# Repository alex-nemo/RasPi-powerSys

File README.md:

# RasPi-powerSys
UPS for Raspberry Pi with power status monitoring

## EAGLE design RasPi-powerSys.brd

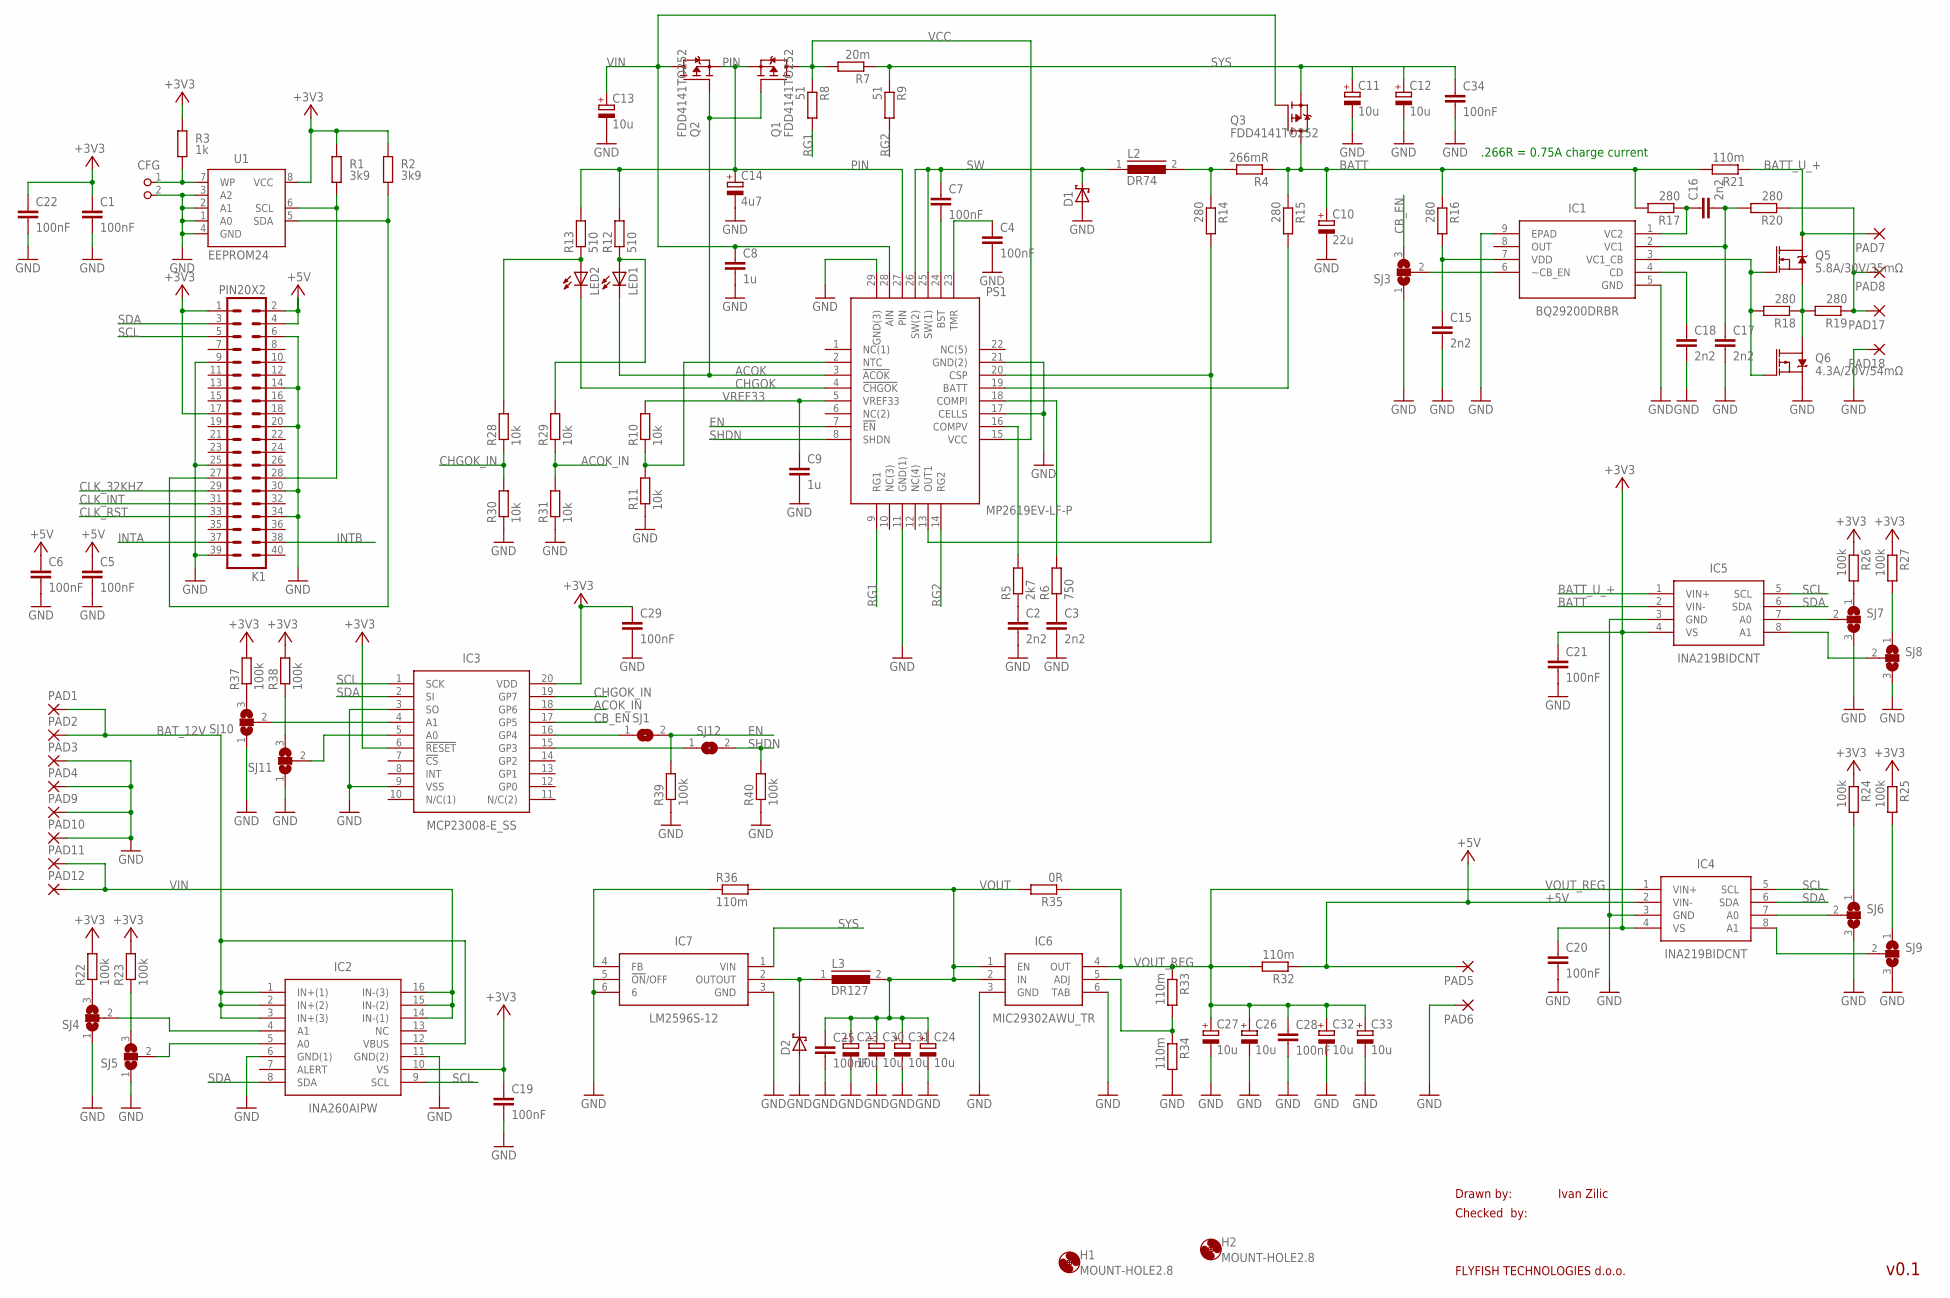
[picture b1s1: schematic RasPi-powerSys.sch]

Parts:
C1, C4, C5, C6, C7, C19, C20, C21, C22, C25, C28, C29, C34: 100nF; C0805K
C2, C3, C15, C16, C17, C18: 2n2; C0805K
C8, C9: 1u; C0805K
C10: 22u; SMC_D
C11, C23, C24, C26, C27, C30, C31, C32, C33: 10u; SMC_E
C12, C13: 10u; SMC_D
C14: 4u7; SMC_D
CFG: PIN2_100; PIN_W_2
D1, D2: SCHOTTKY-DIODESMD; SMB
H1, H2: MOUNT-HOLE2.8; 2,8
IC1: BQ29200DRBR; SON65P300X300X100-9N
IC2: INA260AIPW; SOP65P640X120-16N
IC3: MCP23008-E_SS; SOP65P780X200-20N
IC4, IC5: INA219BIDCNT; SOT65P280X145-8N
IC6: MIC29302AWU_TR; 5-PIN-TO-263(U)
IC7: LM2596S-12; 5-PIN-TO-263(U)
K1: PIN20X2; PIN_20X2
L2: DR74
L3: DR127
LED1, LED2: LEDCHIPLED_0805; CHIPLED_0805
PAD1, PAD2, PAD3, PAD4, PAD5, PAD6, PAD7, PAD8, PAD9, PAD10, PAD11, PAD12, PAD17, PAD18: 3,81/1,4
PS1: MP2619EV-LF-P; QFN50P400X500X100-29N
Q1, Q2, Q3: FDD4141TO252; TO252
Q5: 5.8A/30V/35mΩ; SOT23-3
Q6: 4.3A/20V/54mΩ; SOT23-3
R1, R2: 3k9; M0805; TOLERANCE 5%
R3: 1k; M0805; TOLERANCE 5%
R4: 266mR; R1206
R5: 2k7; R0805
R6: 750; R0805
R7: 20m; R0805
R8, R9: 51; R0805
R10, R11, R28, R29, R30, R31: 10k; R0805
R12, R13: 510; R0805
R14, R15, R16: 280; R0805
R17, R18, R19, R20: 280; R1206
R21, R33, R34, R36: 110m; R0805
R22, R23, R24, R25, R26, R27, R37, R38, R39, R40: 100k; R0805
R32: 110m; R1206
R35: 0R; R1206
SJ1, SJ12: SJ
SJ3, SJ4, SJ5, SJ6, SJ7, SJ8, SJ9, SJ10, SJ11: SJ2W; SJ_2
U1: EEPROM24; SOIC8

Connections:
+3V3: C1.1, C19.1, C20.1, C21.1, C22.1, C29.1, IC2.10 (VS), IC3.6 (!RESET), IC3.20 (VDD), IC4.4 (VS), IC5.4 (VS), K1.1, K1.17, R1.2, R2.2, R3.2, R22.2, R23.2, R24.1, R25.1, R26.1, R27.1, R37.2, R38.2, U1.8 (VCC)
+5V: C5.1, C6.1, IC4.2 (VIN-), K1.2, K1.4, PAD5.1, R32.1
ACOK: LED1.C, PS1.3 (!ACOK), Q1.1 (G), Q2.1 (G)
ACOK_IN: IC3.18 (GP6), R29.1, R31.2
ADJ: IC6.5 (ADJ), R33.2, R34.1
BATT: C10.+, IC5.2 (VIN-), Q3.3 (D), R4.1, R15.1, R16.1, R17.2, R21.2
BATT_U_+: IC5.1 (VIN+), PAD7.1, Q5.3 (D), R21.1
BAT_12V: IC2.1 (IN+(1)), IC2.2 (IN+(2)), IC2.3 (IN+(3)), IC2.12 (VBUS), PAD1.1, PAD2.1
CB_EN: IC3.17 (GP5), SJ3.3
CHGOK: LED2.C, PS1.4 (!CHGOK)
CHGOK_IN: IC3.19 (GP7), R28.1, R30.2
CLK_32KHZ: K1.29
CLK_INT: K1.31
CLK_RST: K1.33
EN: PS1.7 (!EN), R39.2, SJ1.2
GND: C1.2, C2.2, C3.2, C4.2, C5.2, C6.2, C8.2, C9.2, C10.-, C11.-, C12.-, C13.-, C14.-, C15.2, C17.2, C18.2, C19.2, C20.2, C21.2, C22.2, C23.-, C24.-, C25.2, C26.-, C27.-, C28.2, C29.2, C30.-, C31.-, C32.-, C33.-, C34.2, CFG.2, D1.A, D2.A, IC1.5 (GND), IC1.9 (EPAD), IC2.6 (GND(1)), IC2.11 (GND(2)), IC3.3 (SO), IC3.9 (VSS), IC4.3 (GND), IC5.3 (GND), IC6.3 (GND), IC6.6 (TAB), IC7.3 (GND), IC7.5 (!ON!/OFF), IC7.6, K1.6, K1.9, K1.14, K1.20, K1.25, K1.30, K1.34, K1.39, PAD3.1, PAD4.1, PAD6.1, PAD9.1, PAD10.1, PAD18.1, PS1.11 (GND(1)), PS1.17 (CELLS), PS1.21 (GND(2)), PS1.29 (GND(3)), Q6.2 (S), R11.1, R30.1, R31.1, R34.2, R39.1, R40.1, SJ3.1, SJ4.1, SJ5.1, SJ6.3, SJ7.3, SJ8.3, SJ9.3, SJ10.1, SJ11.1, U1.1 (A0), U1.2 (A1), U1.3 (A2), U1.4 (GND)
INTA: K1.37
INTB: K1.38
unnamed: PS1.16 (COMPV), R5.2
unnamed: PS1.18 (COMPI), R6.2
unnamed: CFG.1, R3.1, U1.7 (WP)
unnamed: C2.1, R5.1
unnamed: C3.1, R6.1
unnamed: C4.1, PS1.23 (TMR)
unnamed: IC3.16 (GP4), SJ1.1
unnamed: C15.1, IC1.7 (VDD), R16.2
unnamed: C7.2, PS1.24 (BST)
unnamed: L2.2, R4.2, R14.1
unnamed: IC1.6 (~CB_EN), SJ3.2
unnamed: PS1.2 (NTC), R10.1, R11.2
unnamed: Q5.2 (S), Q6.3 (D), R18.1, R19.2
unnamed: IC3.15 (GP3), SJ12.1
unnamed: PS1.19 (BATT), R15.2
unnamed: LED1.A, R12.1, R29.2
unnamed: K1.28, R1.1, U1.6 (SCL)
unnamed: LED2.A, R13.1, R28.2
unnamed: C18.1, IC1.4 (CD)
unnamed: PS1.13 (OUT1), PS1.20 (CSP), R14.2
unnamed: PAD8.1, PAD17.1, R19.1, R20.1
unnamed: C16.2, C17.1, IC1.2 (VC1), R20.2
unnamed: K1.27, R2.1, U1.5 (SDA)
unnamed: C16.1, IC1.1 (VC2), R17.1
unnamed: IC1.3 (VC1_CB), Q5.1 (G), Q6.1 (G), R18.2
unnamed: IC2.5 (A0), SJ5.2
unnamed: IC2.4 (A1), SJ4.2
unnamed: R22.1, SJ4.3
unnamed: R23.1, SJ5.3
unnamed: R26.2, SJ7.1
unnamed: R27.2, SJ8.1
unnamed: IC4.8 (A1), SJ9.2
unnamed: IC4.7 (A0), SJ6.2
unnamed: IC5.8 (A1), SJ8.2
unnamed: IC5.7 (A0), SJ7.2
unnamed: R37.1, SJ10.3
unnamed: D2.C, IC7.2 (OUTOUT), L3.1
unnamed: R24.2, SJ6.1
unnamed: R25.2, SJ9.1
unnamed: IC7.4 (FB), R36.1
unnamed: IC3.4 (A1), SJ10.2
unnamed: IC3.5 (A0), SJ11.2
unnamed: R38.1, SJ11.3
PIN: C14.+, PS1.27 (PIN), Q1.2 (S), Q2.2 (S), R12.2, R13.2
RG1: PS1.9 (RG1), R8.2
RG2: PS1.14 (RG2), R9.2
SCL: IC2.9 (SCL), IC3.1 (SCK), IC4.5 (SCL), IC5.5 (SCL), K1.5
SDA: IC2.8 (SDA), IC3.2 (SI), IC4.6 (SDA), IC5.6 (SDA), K1.3
SHDN: PS1.8 (SHDN), R40.2, SJ12.2
SW: C7.1, D1.C, L2.1, PS1.25 (SW(1)), PS1.26 (SW(2))
SYS: C11.+, C12.+, C34.1, IC7.1 (VIN), Q3.2 (S), R7.1, R9.1
VCC: PS1.15 (VCC), Q1.3 (D), R7.2, R8.1
VIN: C8.1, C13.+, IC2.14 (IN-(1)), IC2.15 (IN-(2)), IC2.16 (IN-(3)), PAD11.1, PAD12.1, PS1.28 (AIN), Q2.3 (D), Q3.1 (G)
VOUT: C23.+, C24.+, C25.1, C30.+, C31.+, IC6.1 (EN), IC6.2 (IN), L3.2, R35.2, R36.2
VOUT_REG: C26.+, C27.+, C28.1, C32.+, C33.+, IC4.1 (VIN+), IC6.4 (OUT), R32.2, R33.1, R35.1
VREF33: C9.1, PS1.5 (VREF33), R10.2

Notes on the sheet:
Drawn by:
Checked by:
FLYFISH TECHNOLOGIES d.o.o.
Ivan Zilic
v0.1
.266R = 0.75A charge current

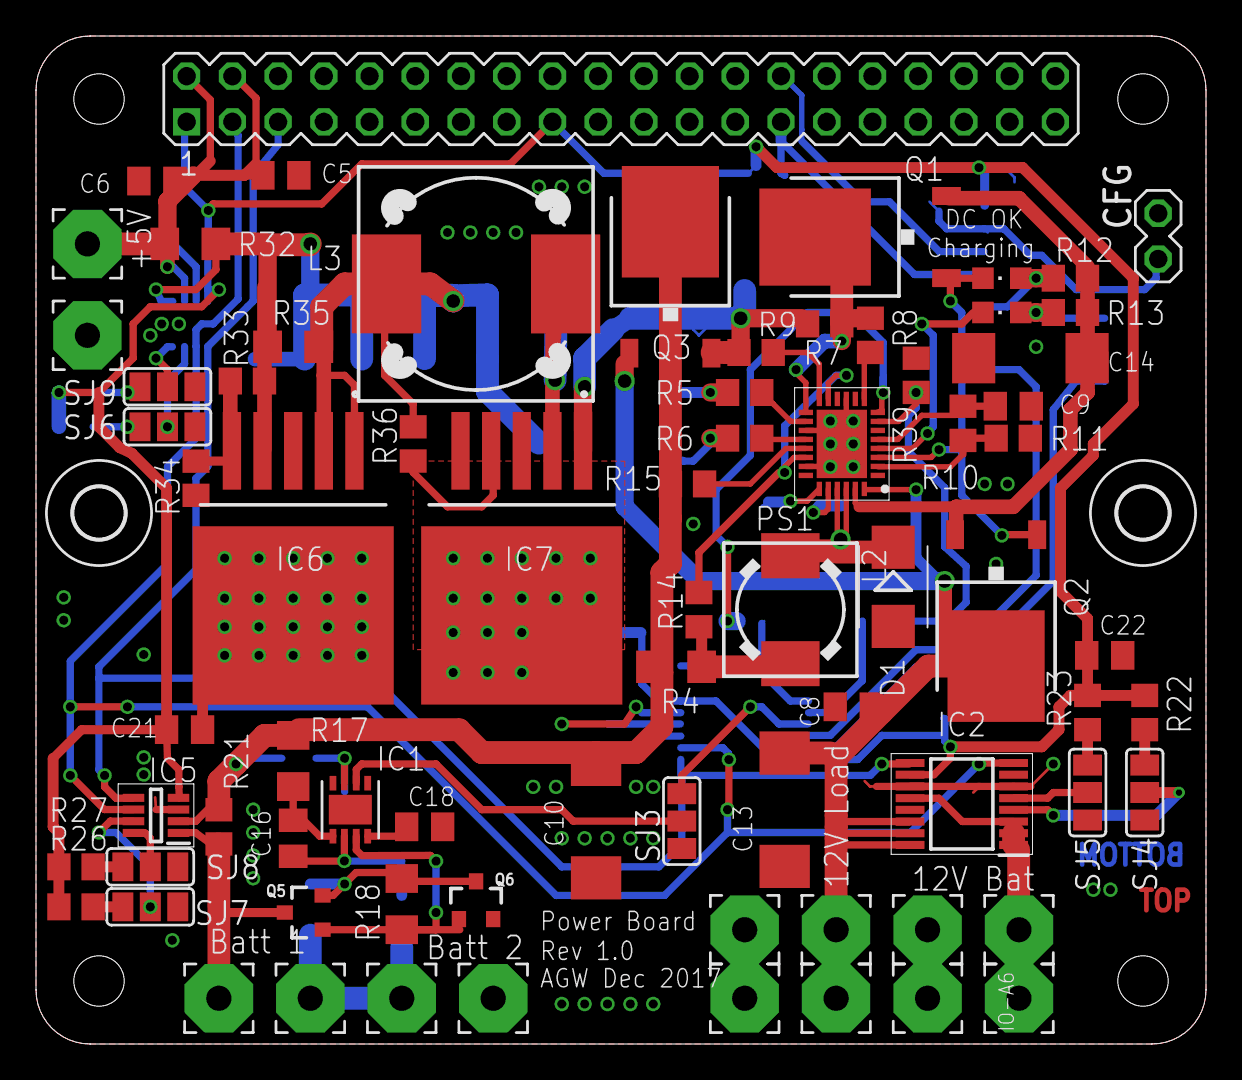
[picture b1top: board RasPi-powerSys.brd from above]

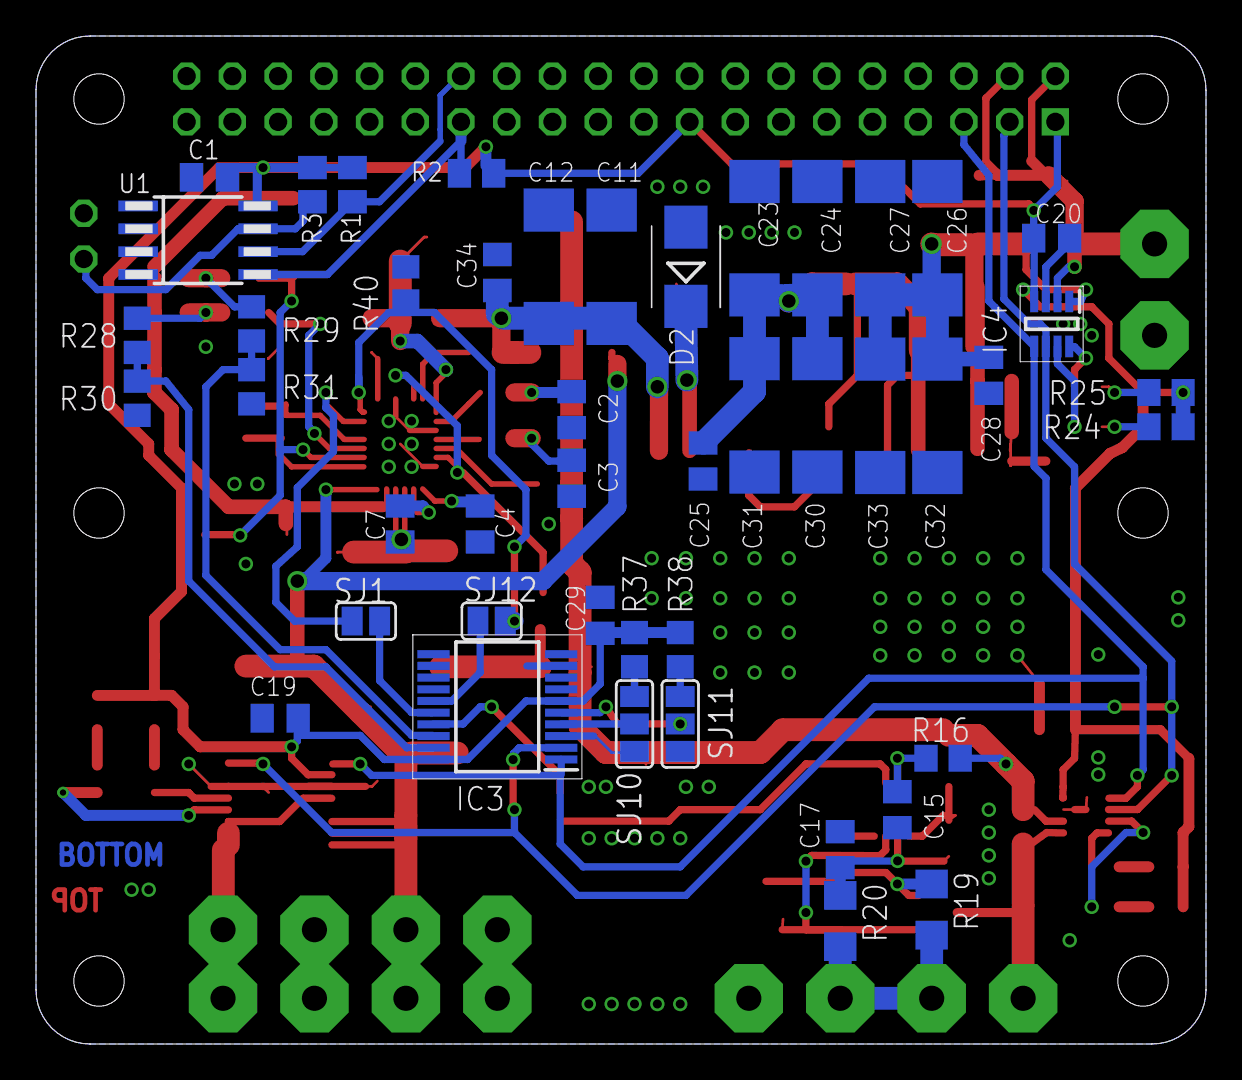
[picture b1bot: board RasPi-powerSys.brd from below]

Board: 2 copper layers, 65.0 x 56.0 mm, 123 parts (46 on the bottom side), 69 nets.

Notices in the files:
parts and their libraries:
SparkFun-DiscreteSemi: Licensing: Creative Commons ShareAlike 4.0 International - https://creativecommons.org/licenses/by-sa/4.0
